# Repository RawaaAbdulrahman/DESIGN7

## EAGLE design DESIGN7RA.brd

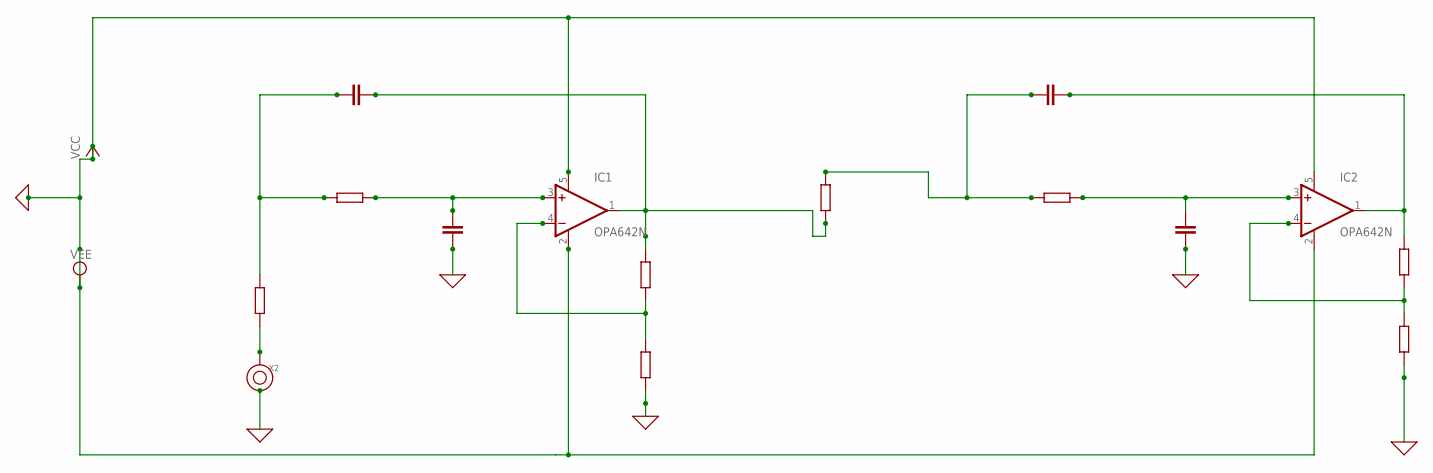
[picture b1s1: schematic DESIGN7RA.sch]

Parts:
IC1, IC2: OPA642N; SOT23-5
X2: BINDING-POST

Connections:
0: IC1.2 (V-), IC1.5 (V+), IC2.2 (V-), IC2.5 (V+)
unnamed: X2.1, X2.1_1, X2.1_2, X2.1_3, X2.1_4, X2.1_5, X2.1_6, X2.1_7, X2.1_8

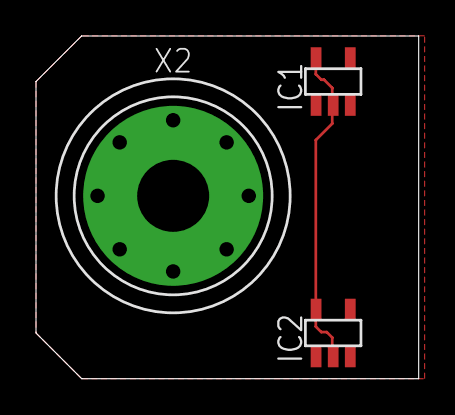
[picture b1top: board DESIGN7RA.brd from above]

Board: 2 copper layers, 21.3 x 19.0 mm, 3 parts (0 on the bottom side), 2 nets.
